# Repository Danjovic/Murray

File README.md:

# Murray
SNES to dual Joystick adapter for Atari 5200 

This adapter was named after The 8 Bit Guy that came with a SNES layout for a game that he is developing (for Commodore PET/64) that have controls very similar to Robotron, where the directional Pad controls the movement while the X Y A B buttons control the shooting direction.

## Button Mapping

Full keyboard control is provided using the SELECT and START buttons as Alt/Modifiers keys.

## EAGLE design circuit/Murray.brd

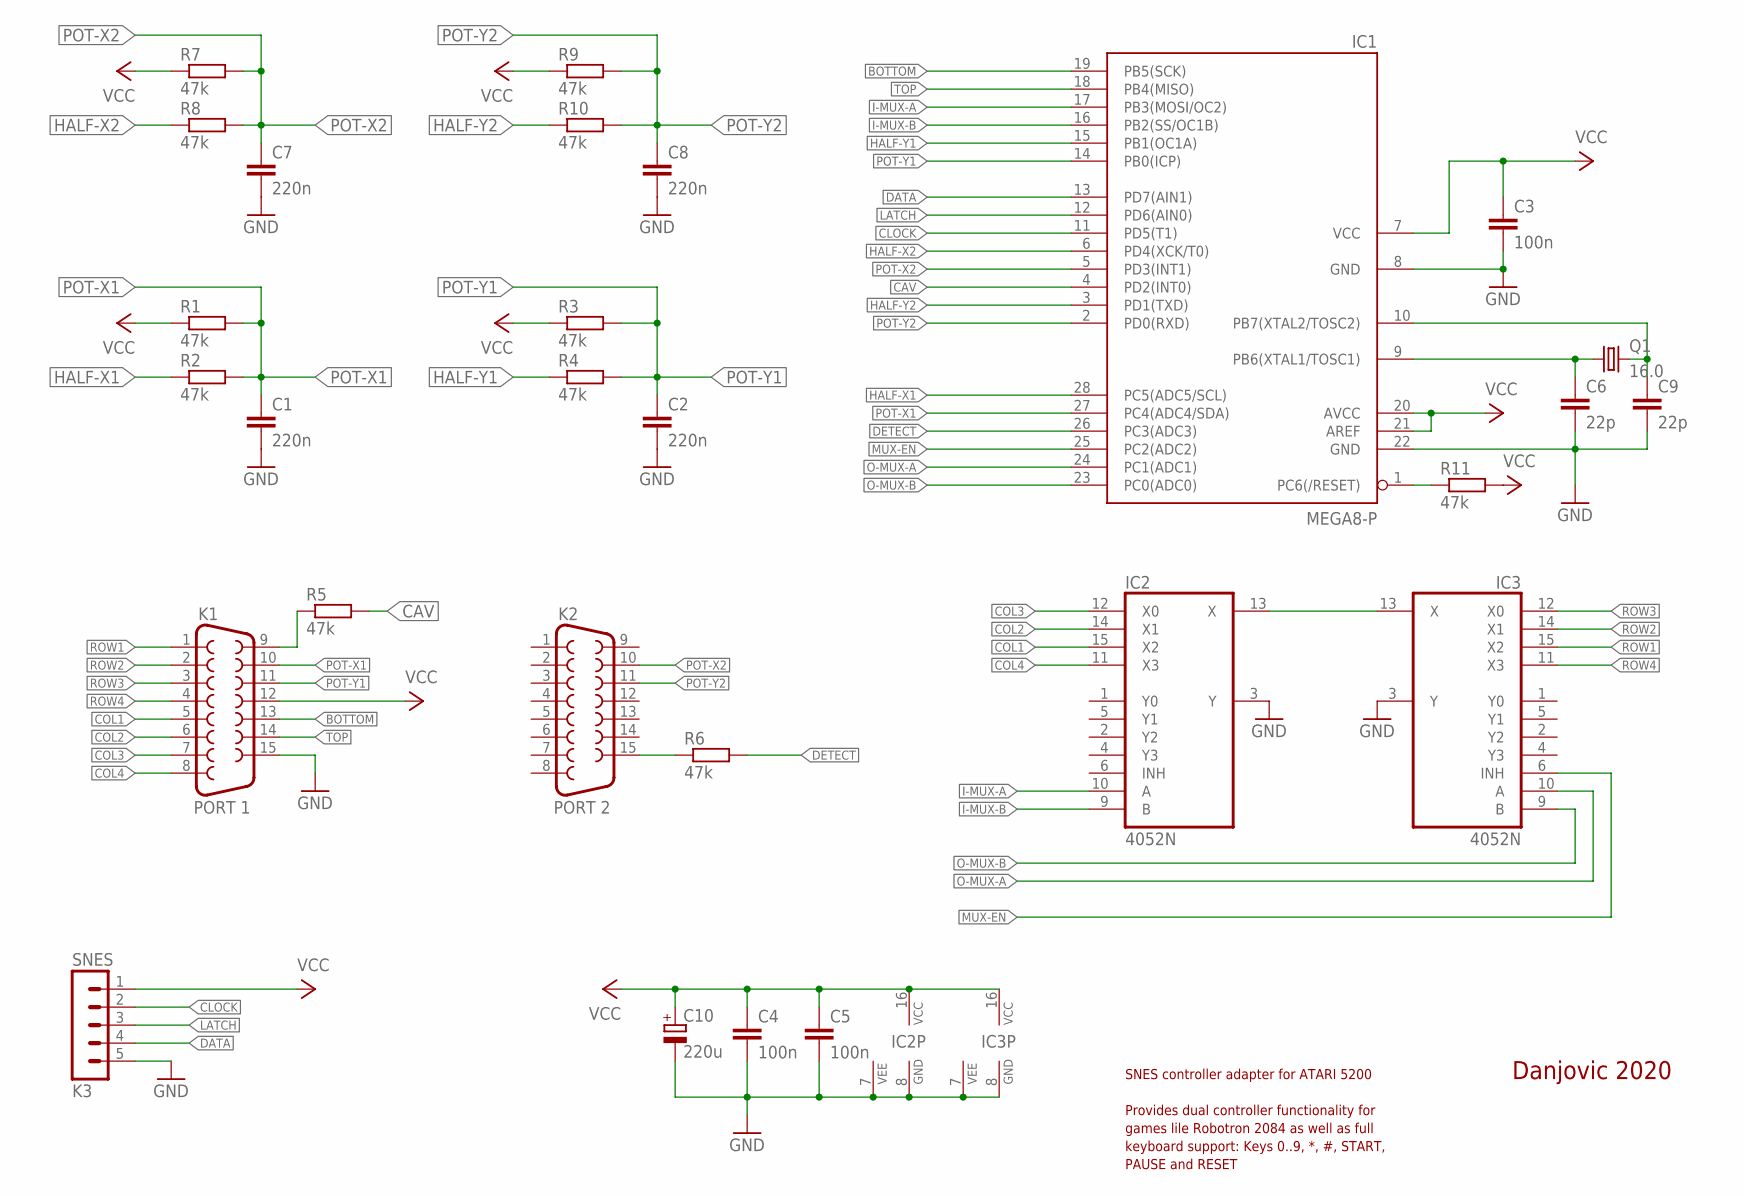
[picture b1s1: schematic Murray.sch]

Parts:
C1, C2, C7, C8: 220n; C050-030X075
C3, C4, C5: 100n; C050-024X044
C6, C9: 22p; C025-024X044
C10: 220u; E2,5-6E
IC1: MEGA8-P; DIL28-3
IC2, IC3: 4052N; DIL16
K1: PORT 1; F15H
K2: PORT 2; F15H
K3: SNES; MA05-1
Q1: 16.0; TC26V
R1, R2, R3, R4, R5, R6, R7, R8, R9, R10, R11: 47k; 0204/7

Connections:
BOTTOM: IC1.19 (PB5(SCK)), K1.13
CAV: IC1.4 (PD2(INT0)), R5.2
CLOCK: IC1.11 (PD5(T1)), K3.2
COL1: IC2.15 (X2), K1.5
COL2: IC2.14 (X1), K1.6
COL3: IC2.12 (X0), K1.7
COL4: IC2.11 (X3), K1.8
DATA: IC1.13 (PD7(AIN1)), K3.4
DETECT: IC1.26 (PC3(ADC3)), R6.2
GND: C1.2, C2.2, C3.2, C4.2, C5.2, C6.2, C7.2, C8.2, C9.2, C10.-, IC1.8 (GND), IC1.22 (GND), IC2.3 (Y), IC2.7 (VEE), IC2.8 (GND), IC3.3 (Y), IC3.7 (VEE), IC3.8 (GND), K1.15, K3.5
HALF-X1: IC1.28 (PC5(ADC5/SCL)), R2.1
HALF-X2: IC1.6 (PD4(XCK/T0)), R8.1
HALF-Y1: IC1.15 (PB1(OC1A)), R4.1
HALF-Y2: IC1.3 (PD1(TXD)), R10.1
I-MUX-A: IC1.17 (PB3(MOSI/OC2)), IC2.10 (A)
I-MUX-B: IC1.16 (PB2(SS/OC1B)), IC2.9 (B)
LATCH: IC1.12 (PD6(AIN0)), K3.3
MUX-EN: IC1.25 (PC2(ADC2)), IC3.6 (INH)
unnamed: K2.15, R6.1
unnamed: IC2.13 (X), IC3.13 (X)
unnamed: IC1.1 (PC6(/RESET)), R11.1
unnamed: K1.9, R5.1
O-MUX-A: IC1.24 (PC1(ADC1)), IC3.10 (A)
O-MUX-B: IC1.23 (PC0(ADC0)), IC3.9 (B)
POT-X1: C1.1, IC1.27 (PC4(ADC4/SDA)), K1.10, R1.2, R2.2
POT-X2: C7.1, IC1.5 (PD3(INT1)), K2.10, R7.2, R8.2
POT-Y1: C2.1, IC1.14 (PB0(ICP)), K1.11, R3.2, R4.2
POT-Y2: C8.1, IC1.2 (PD0(RXD)), K2.11, R9.2, R10.2
ROW1: IC3.15 (X2), K1.1
ROW2: IC3.14 (X1), K1.2
ROW3: IC3.12 (X0), K1.3
ROW4: IC3.11 (X3), K1.4
TOP: IC1.18 (PB4(MISO)), K1.14
VCC: C3.1, C4.1, C5.1, C10.+, IC1.7 (VCC), IC1.20 (AVCC), IC1.21 (AREF), IC2.16 (VCC), IC3.16 (VCC), K1.12, K3.1, R1.1, R3.1, R7.1, R9.1, R11.2
XT1: C6.1, IC1.9 (PB6(XTAL1/TOSC1)), Q1.1
XT2: C9.1, IC1.10 (PB7(XTAL2/TOSC2)), Q1.2

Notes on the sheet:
SNES controller adapter for ATARI 5200
Danjovic 2020
Provides dual controller functionality for
games lile Robotron 2084 as well as full
keyboard support: Keys 0..9, *, #, START,
PAUSE and RESET

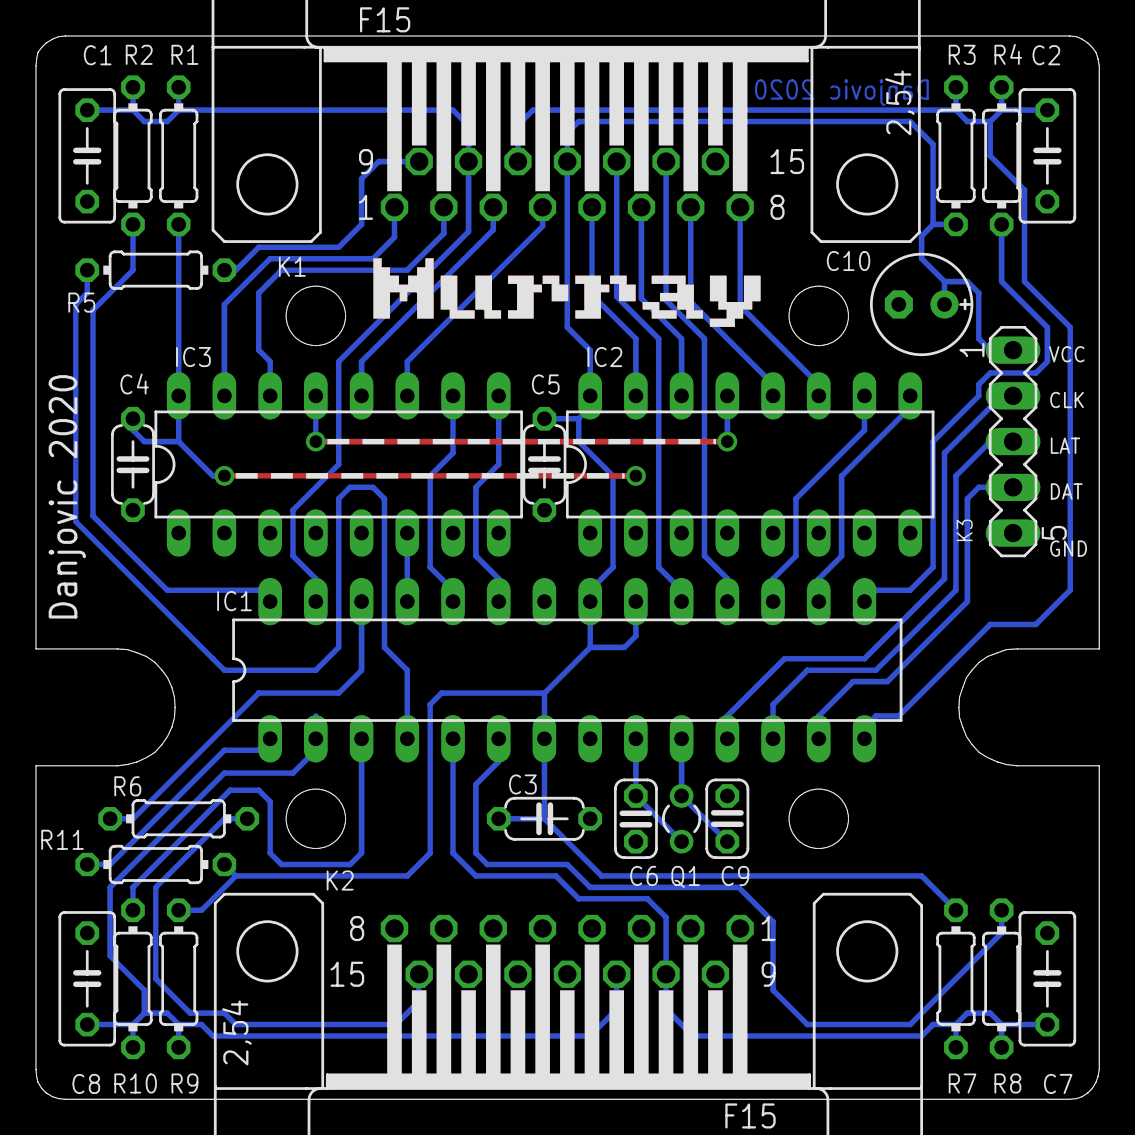
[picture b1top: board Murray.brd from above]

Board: 2 copper layers, 59.1 x 59.1 mm, 29 parts (0 on the bottom side), 36 nets.

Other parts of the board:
U$1: 1593J

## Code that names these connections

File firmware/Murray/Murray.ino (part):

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   1 1  | start | pause | reset |  none | 4
        +-------+-------+-------+-------+

  CAV Voltage on PIN 9 is connected to INT0 IRQ pin and is used to promptly turn off the timing pins whenever CAV drops to zero.
  A resistor is added to protect the AVR input, as the CAV voltage can reach up to 6.4Volts.

  Pinout:

  FUNCTION  ARDUINO AVR                       AVR  ARDUINO  FUNCTION
                            +---\__/---+
                    RST  [ 1]          [28]   PC5    A5/D19   HALF-X1
   POT-Y2     D0    PD0  [ 2]          [27]   PC4    A4/D18   POT-X1
   HALF-Y2    D1    PD1  [ 3]          [26]   PC3    A3/D17   DETECT PORT2
   VAC        D2    PD2  [ 4]INT0      [25]   PC2    A2/D16   MUX-ENABLE
   POT-X2     D3    PD3  [ 5]          [24]   PC1    A1/D15   O-MUX-A
   HALF-X2    D4    PD4  [ 6]          [23]   PC0    A0/D14   O-MUX-B
                    VCC  [ 7]          [22]   GND
                    GND  [ 8]          [21]   AREF
                    XT1  [ 9]          [20]   AVCC
                    XT2  [10]          [19]   PB5    D13      BOTTOM
  SNES CLOCK  D5    PD5  [11]          [18]   PB4    D13      TOP
  SNES LATCH  D6    PD6  [12]          [17]   PB3    D11      I-MUX-B
  SNES DATA   D7    PD7  [12]          [16]   PB2    D10      I-MUX-A
   POT-Y1     D8    PB0  [14]          [15]   PB1    D9       HALF-Y1
                            +----------+


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       |_|_||_\__\___|_| |_|  \_,_| .__/\__/__/
                                  |_|
*/
// Pin change interrupt, trigger by Cav line change state.
ISR (PCINT0_vect) {
  if ( CAVinput() ) {  // rising edge ?

    CAVoff = 0;    // flag that CAV voltage is present

  } else { // Falling edge

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    potX2low();
    potY2low();

    CAVoff = 1; // flag that CAV voltage has dropped
  }
}

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  // initialize Atari 5200 interface
  setIdleState();

  DDRcavSignal &= ~(1 << BITcavSignal); // CAV detection pin as input
  PORTcavSignal &= ~(1 << BITcavSignal); // no pullup

  DDRdetect2ndPort &= ~(1 << BITdetect2ndPort); // detection pin as input
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  PORTdataSignal  |= (1 << BITdataSignal);  // Pullup enabled

  // initialize interrupts
  // Setup Pin Change Interrupt for Cav
  PCICR =   (0 << PCIE0)    // Pin change interrupt enable for  PCINT0..PCINT7   at pins PB0..PB7
            | (0 << PCIE1)    // Pin change interrupt enable for  PCINT8..PCINT14  at pins PC0..PC6
            | (1 << PCIE2);   // Pin change interrupt enable for PCINT16..PCINT23  at pins PD0..PD7

  PCMSK2 =   (0 << PCINT16)  // Pin change enable for PD0 pin
             | (0 << PCINT17)  // Pin change enable for PD1 pin
             | (1 << PCINT18)  // Pin change enable for PD2 pin - Vac voltage is connected here
             | (0 << PCINT19)  // Pin change enable for PD3 pin
             | (0 << PCINT20)  // Pin change enable for PD4 pin
             | (0 << PCINT21)  // Pin change enable for PD5 pin
             | (0 << PCINT22)  // Pin change enable for PD6 pin
             | (0 << PCINT23); // Pin change enable for PD7 pin


  PCIFR =   (0 << PCIF0) // Clear any pending interrupt flag
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
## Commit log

2020-10-04 Added directive to support NES clone controllers

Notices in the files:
firmware/Murray/Murray.ino:
This program is free software: you can redistribute it and/or modify
it under the terms of the GNU General Public License as published by
the Free Software Foundation, either version 3 of the License, or
(at your option) any later version.
